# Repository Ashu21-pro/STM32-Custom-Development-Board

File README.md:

# STM32 Custom Development Board — KiCad PCB Design

## Overview
This repository contains the schematic and PCB layout for a custom STM32-based development board designed in KiCad. The design includes a microcontroller circuit, power-supply circuitry, decoupling components, and UART and SWD connectors.

## Features
- STM32 microcontroller-based design
- On-board power-supply circuitry
- UART connector for serial communication
- SWD connector for programming and debugging
- Routed PCB layout
- Four mounting holes
- 3D PCB visualization

## Tools Used
- KiCad Schematic Editor
- KiCad PCB Editor
- KiCad 3D Viewer

## Repository Structure
```text
STM32-Custom-Development-Board/
├── README.md
├── Design_Files/
│   ├── STM32PCB.kicad_pro
│   ├── STM32PCB.kicad_sch
│   └── STM32PCB.kicad_pcb
├── Images/
│   ├── pcb_3d_view.png
│   ├── pcb_layout.png
│   ├── schematic.png
│   └── pcb_fabrication_view.png
└── Documentation/
    └── BOM.csv
```

> Replace the example KiCad filenames with your actual filenames. The `Documentation/` folder and BOM are optional; include them only if you have those files.

## Validation and Testing
Record the KiCad Design Rule Check (DRC) results here. Add electrical testing and hardware validation results after completing them.

## Project Status
PCB layout designed in KiCad. Manufacturing and hardware testing status: update as applicable.

## Author
Ashutosh K. Undure

## License
No license has been specified. Add an appropriate license if you want others to reuse or modify this design.

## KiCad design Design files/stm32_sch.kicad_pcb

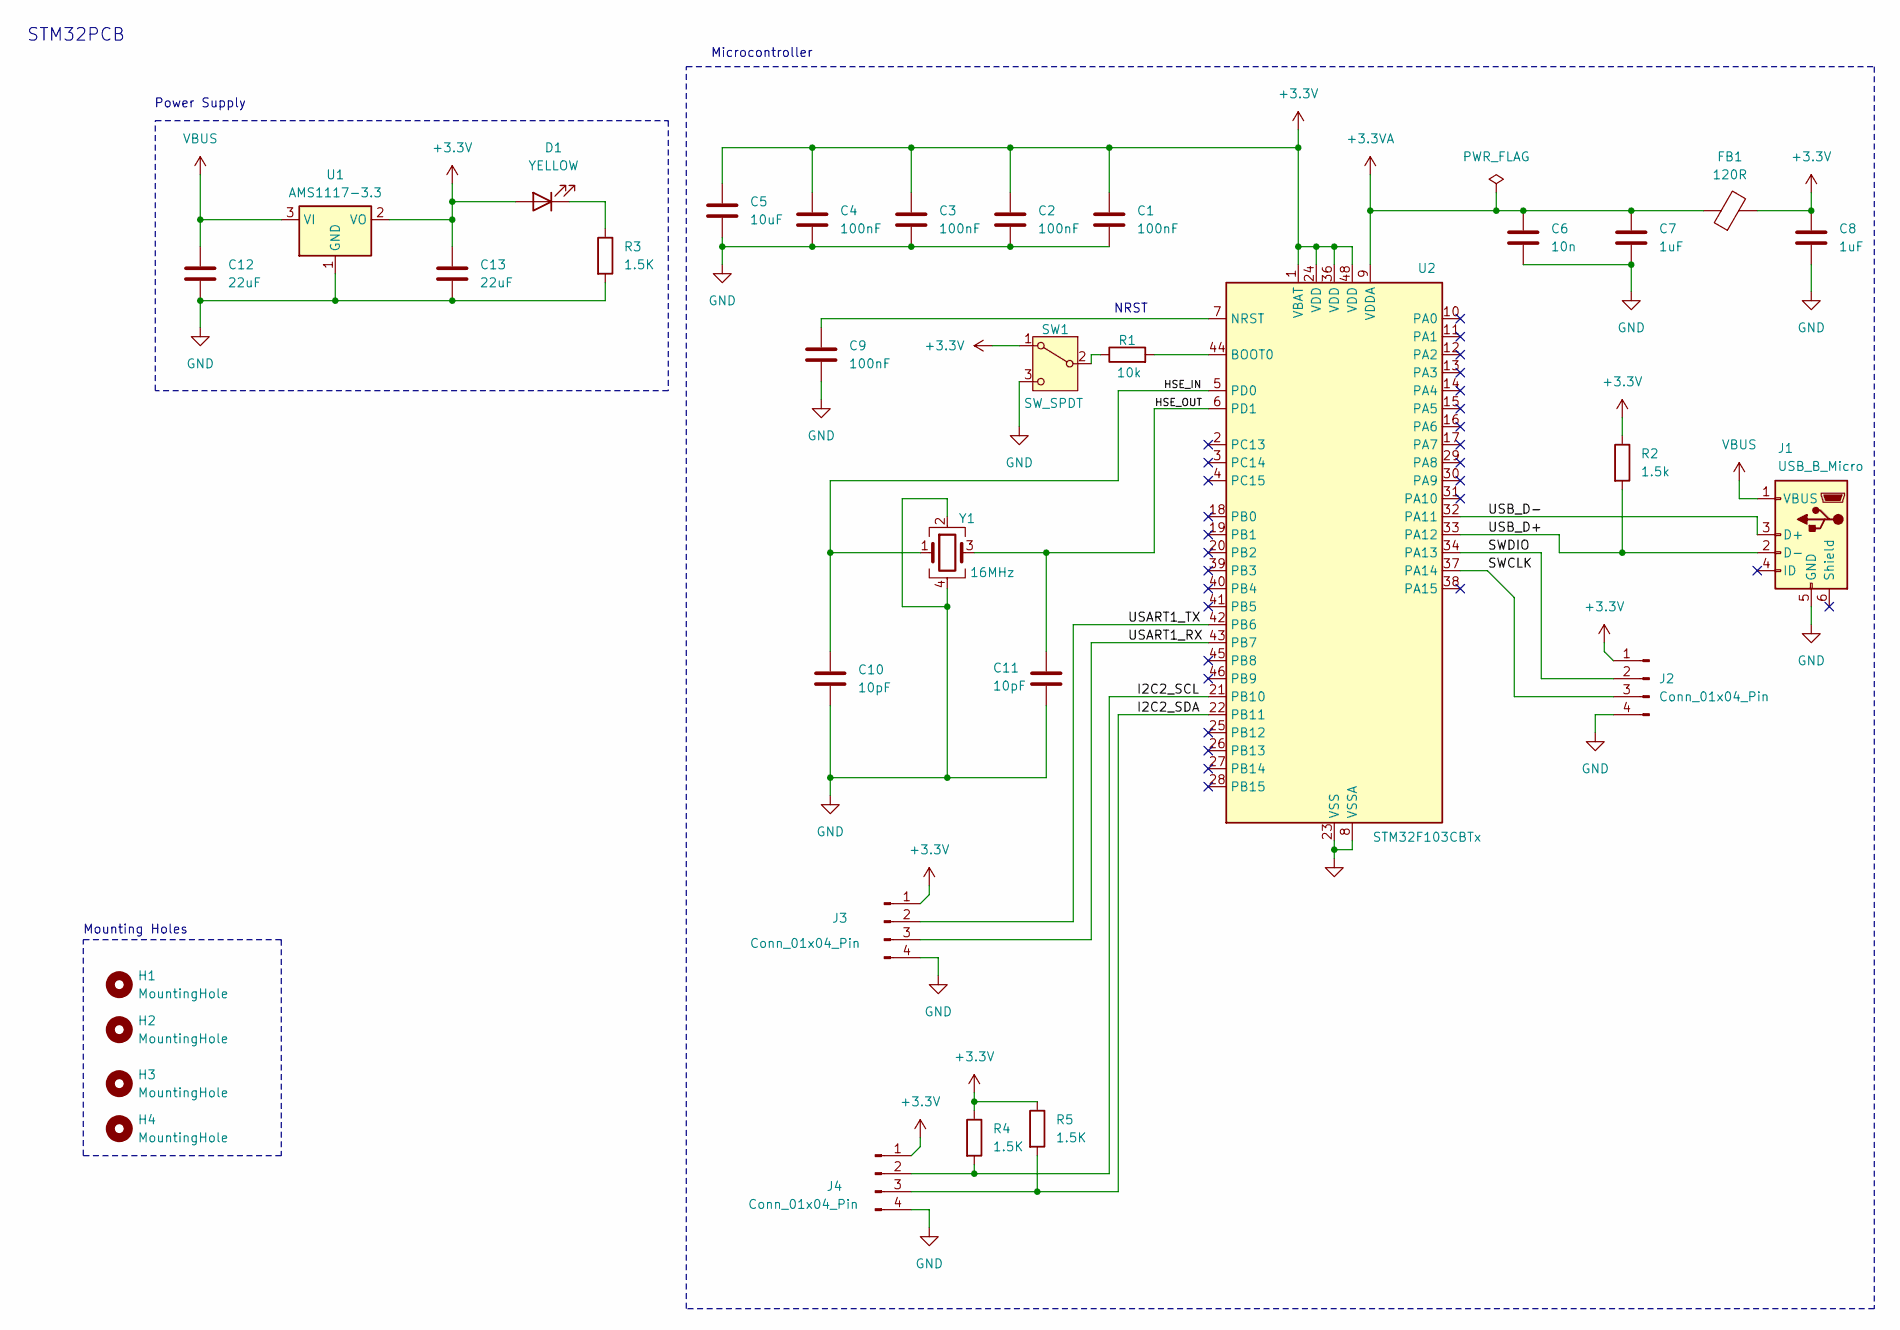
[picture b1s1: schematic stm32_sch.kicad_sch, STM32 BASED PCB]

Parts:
C1, C2: 100nF; C_0805_2012Metric
C3: 100nF; C_0603_1608Metric
C4, C9: 100nF; C_0402_1005Metric
C5: 10uF; C_0402_1005Metric
C6: 10n; C_0402_1005Metric
C7, C8: 1uF; C_0402_1005Metric
C10, C11: 10pF; C_0402_1005Metric
C12, C13: 22uF; C_0402_1005Metric
D1: YELLOW; LED_0603_1608Metric
FB1: 120R; L_0603_1608Metric
H1, H2, H3, H4: MountingHole; MountingHole_2.2mm_M2
J1: USB_B_Micro; USB_Micro-B_Wuerth_614105150721_Vertical
J2, J3, J4: Conn_01x04_Pin; PinHeader_1x04_P2.54mm_Vertical
R1: 10k; R_0402_1005Metric
R2: 1.5k; R_0402_1005Metric
R3, R4, R5: 1.5K; R_0402_1005Metric
SW1: SW_SPDT; SW_SPDT_PCM12
U1: AMS1117-3.3; SOT-223-3_TabPin2
U2: STM32F103CBTx; LQFP-48_7x7mm_P0.5mm
Y1: 16MHz; Crystal_SMD_3225-4Pin_3.2x2.5mm

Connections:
+3.3V: C1.1, C2.1, C3.1, C4.1, C5.1, C8.1, C13.1, D1.2 (A), FB1.2, J2.1, J3.1, J4.1, R2.1, R4.1, R5.1, SW1.1 (A), U1.2 (VO), U2.1 (VBAT), U2.24 (VDD), U2.36 (VDD), U2.48 (VDD)
+3.3VA: C6.1, C7.1, FB1.1, U2.9 (VDDA)
/HSE_IN: C10.1, U2.5 (PD0), Y1.1
/HSE_OUT: C11.1, U2.6 (PD1), Y1.3
/I2C2_SCL: J4.2, R4.2, U2.21 (PB10)
/I2C2_SDA: J4.3, R5.2, U2.22 (PB11)
/SWCLK: J2.3, U2.37 (PA14)
/SWDIO: J2.2, U2.34 (PA13)
/USART1_RX: J3.3, U2.43 (PB7)
/USART1_TX: J3.2, U2.42 (PB6)
/USB_D+: J1.2 (D-), R2.2, U2.33 (PA12)
/USB_D-: J1.3 (D+), U2.32 (PA11)
GND: C1.2, C2.2, C3.2, C4.2, C5.2, C6.2, C7.2, C8.2, C9.2, C10.2, C11.2, C12.2, C13.2, J1.5 (GND), J2.4, J3.4, J4.4, R3.2, SW1.3 (C), U1.1 (GND), U2.8 (VSSA), U2.23 (VSS), U2.35 (VSS), U2.47 (VSS), Y1.2, Y1.4
unnamed: D1.1 (K), R3.1
unnamed: R1.1, SW1.2 (B)
unnamed: R1.2, U2.44 (BOOT0)
unnamed: C9.1, U2.7 (NRST)
VBUS: C12.1, J1.1 (VBUS), U1.3 (VI)

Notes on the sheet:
Mounting Holes
NRST
Power Supply
Microcontroller
STM32PCB

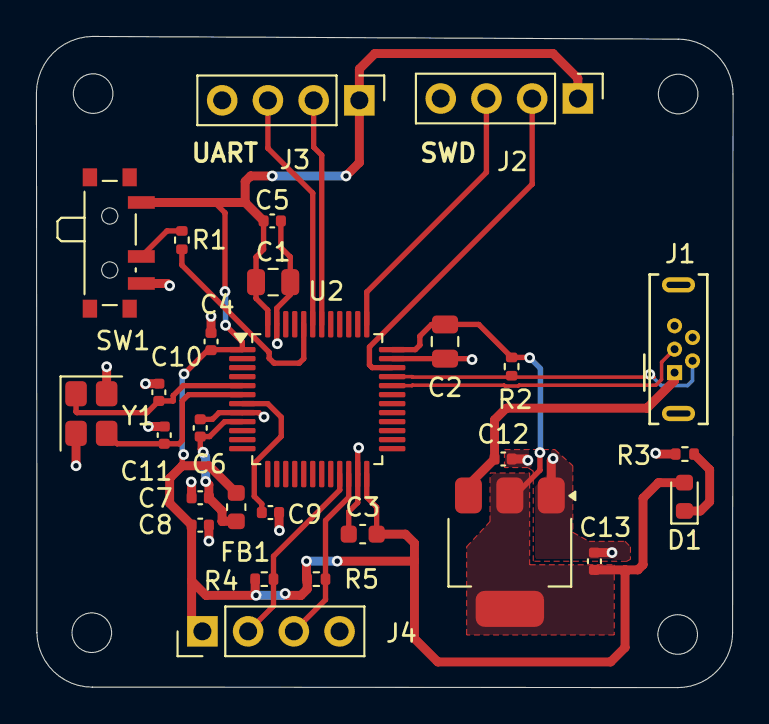
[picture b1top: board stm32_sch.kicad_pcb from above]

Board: 2 copper layers, 38.7 x 36.2 mm, 32 parts (0 on the bottom side), 18 nets.
